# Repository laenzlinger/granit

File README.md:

# Granit — Offsite Backup Device

Custom carrier board for the Raspberry Pi CM4 Compute Module, designed as a minimal offsite backup appliance.

📖 **[Documentation](https://laenzlinger.github.io/granit/latest/)**

## Overview

A compact, headless device that connects to a remote network and receives encrypted backups
onto an attached hard disk. Designed to be left at a trusted offsite location and managed remotely.

- Raspberry Pi CM4 with PCIe SATA (ASM1061)
- 2.5" or 3.5" HDD/SSD support
- Software-controlled HDD power (GPIO)
- RTC wake for scheduled backups
- USB-C OTG for eMMC flashing
- Hammond 1455 aluminium enclosure

## Roadmap

- **v0.3** — First production run (CM4, 4-layer PCB, JLCPCB)
- **v0.4** — Fix wake/shutdown latch (#31), barrel jack swap (#40), DF40C alignment bosses (#37)
- **v1.0** — Validated design with custom OS image and documentation
- **Future** — Investigating RISC-V SoM support for a fully blob-free variant

## License

[CERN Open Hardware Licence Version 2 - Permissive](https://ohwr.org/cern_ohl_p_v2.txt)

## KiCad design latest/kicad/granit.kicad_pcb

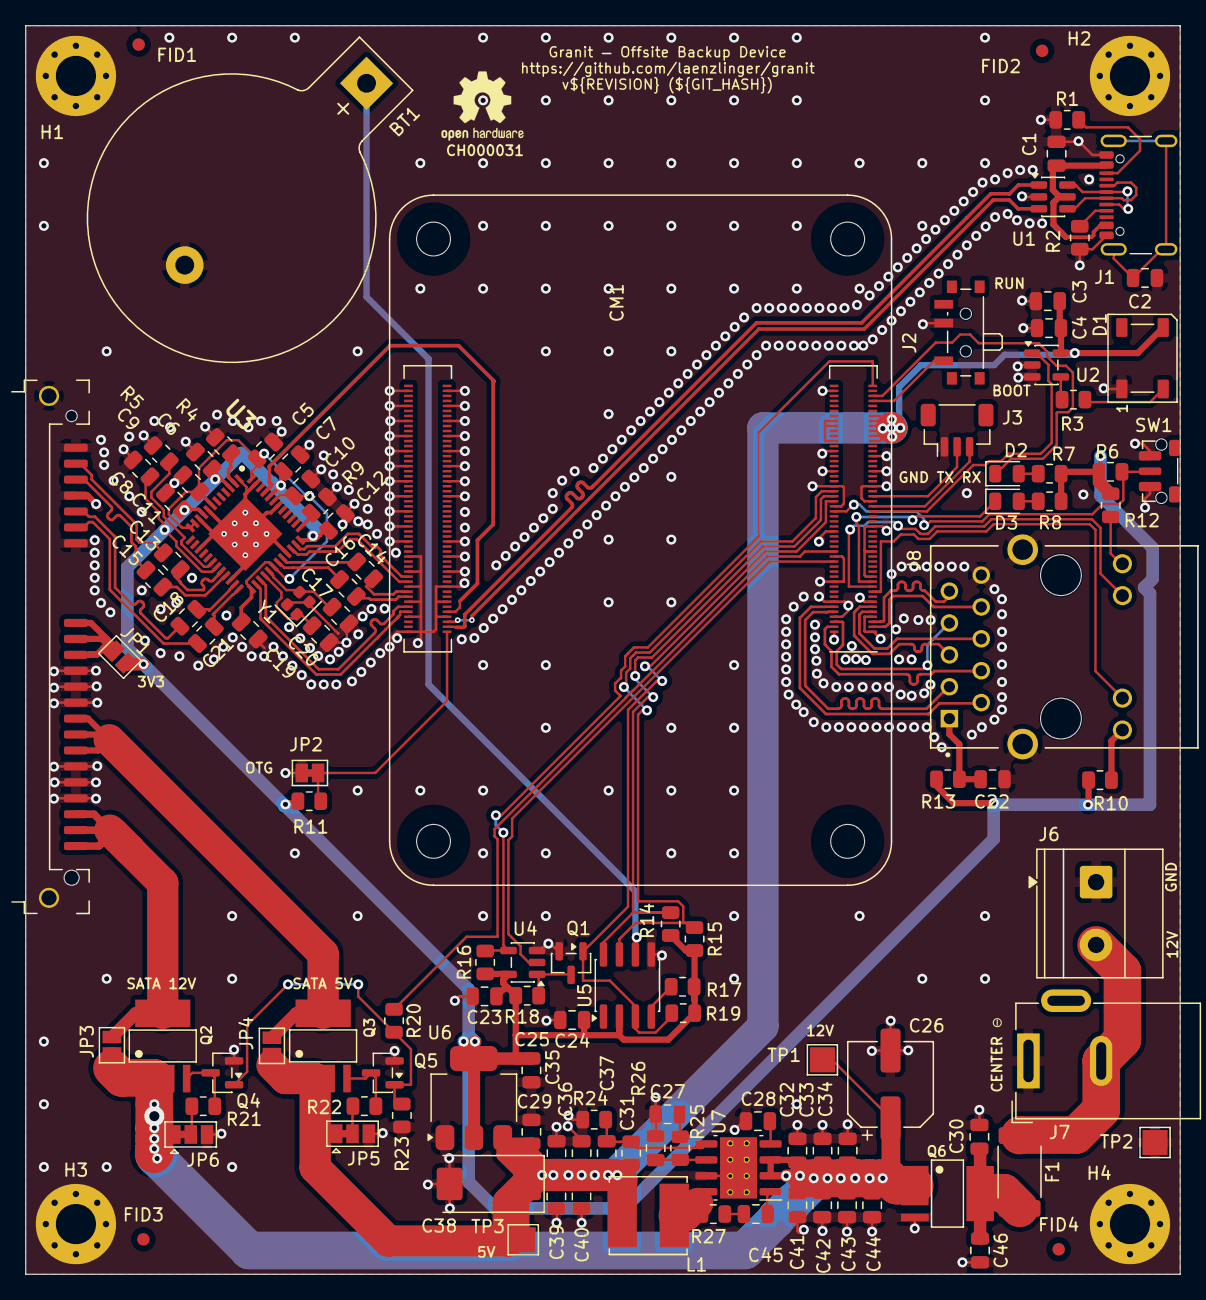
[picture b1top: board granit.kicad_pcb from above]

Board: 4 copper layers, 92.0 x 99.5 mm, 120 parts (0 on the bottom side), 87 nets.

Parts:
BT1: CR2032; BatteryHolder_Keystone_103_1x20mm
C1, C2, C3, C4, C5, C6, C7, C8, C9, C10, C11, C12, C13, C14, C15, C16, C18, C19, C21, C22, C23, C24, C28, C45: 100n; C_0805_2012Metric
C17, C20: 18p; C_0805_2012Metric
C25, C29, C30, C32, C33, C34, C35, C36, C39, C40, C41, C42, C43, C44, C46: 10u; C_0805_2012Metric
C26: 100uF/25V; CP_Elec_6.3x7.7
C27: 1.2n; C_0805_2012Metric
C31, C37: 1n; C_0805_2012Metric
C38: 100u; CP_EIA-7343-31_Kemet-D
CM1: CM4; Raspberry-Pi-4-Compute-Module
D1: WS2812B-5mm; LED_WS2812B_PLCC4_5.0x5.0mm_P3.2mm
D2: LED R; LED_0805_2012Metric
D3: LED G; LED_0805_2012Metric
F1: 3A; Fuse_2512_6332Metric
FID1, FID2, FID3, FID4: Fiducial; Fiducial_1mm_Mask2mm
H1, H2, H3, H4: MountingHole; MountingHole_3.2mm_M3_Pad_Via
J1: USB_C_Receptacle_USB2.0_14P; USB_C_Receptacle_GCT_USB4105-xx-A_16P_TopMnt_Horizontal
J2: PCM12SMTR; SW_SPDT_PCM12
J3: BM03B-SRSS-TB; JST_SH_BM03B-SRSS-TB_1x03-1MP_P1.00mm_Vertical
J4: SATA_22pin; SATA_Amphenol_10029364-001LF_Horizontal
J6: 12V Screw Terminal; TerminalBlock_Phoenix_MKDS-1,5-2_1x02_P5.00mm_Horizontal
J7: 12V Barrel; BarrelJack_Wuerth_6941xx301002
J8: HR911130A; HANRUN_HR911130A
JP1: 3V3_bridge; SolderJumper-2_P1.3mm_Open_Pad1.0x1.5mm
JP2: USB_OTG; SolderJumper-2_P1.3mm_Bridged_Pad1.0x1.5mm
JP3: 12V_bridge; SolderJumper-2_P1.3mm_Open_Pad1.0x1.5mm
JP4: 5V_bridge; SolderJumper-2_P1.3mm_Open_Pad1.0x1.5mm
JP5: SATA_5V_PWR; SolderJumper-3_P1.3mm_Bridged12_Pad1.0x1.5mm
JP6: SATA_12V_PWR; SolderJumper-3_P1.3mm_Bridged12_Pad1.0x1.5mm
L1: SRN6045TA-3R3Y; L_Bourns_SRN6045TA
Q1, Q4, Q5: 2N7002; SOT-23
Q2, Q3, Q6: FDS4435BZ; SO08-E3
R1, R2: 5K1; R_0805_2012Metric
R3, R7, R8, R10, R12: 330R; R_0805_2012Metric
R4, R26: 12K; R_0805_2012Metric
R5, R9: 750R; R_0805_2012Metric
R6, R11, R16, R17, R18, R19, R20: 10K; R_0805_2012Metric
R13, R27: 10R; R_0805_2012Metric
R14, R15: 4K7; R_0805_2012Metric
R21, R22, R23: 100K; R_0805_2012Metric
R24: 2K2; R_0805_2012Metric
R25: 20K; R_0805_2012Metric
SW1: SW_Push; SW_Push_1P1T-MP_NO_Horizontal_Alps_SKRTLAE010
SYM1: Logo_Open_Hardware_Large; OSHW-Logo2_7.3x6mm_SilkScreen
TP1, TP2, TP3: TestPoint; TestPoint_Pad_2.0x2.0mm
U1: USBLC6-2SC6; SOT-23-6
U2: 74AHCT1G125; SOT-23-5
U3: ASM1061; QFN50P700X700X90-49N-D
U4: 74AHCT1G32; SOT-23-5
U5: DS3231MZ; SOIC-8_3.9x4.9mm_P1.27mm
U6: NCP1117-3.3_SOT223; SOT-223-3_TabPin2
U7: AP64501SP-13; SOIC-8-1EP_3.9x4.9mm_P1.27mm_EP2.95x4.9mm_Mask2.71x3.4mm_Th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
Y1: 25MHz; Crystal_SMD_2016-4Pin_2.0x1.6mm

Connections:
+3V3: C6.1, C7.1, C8.1, C11.1, C12.1, C23.1, C24.1, C25.1, JP1.2 (B), R6.1, R7.2, R8.2, R10.1, R11.1, R12.1, R13.1, R14.2, R15.2, R16.1, R17.1, R18.1, R19.2, U3.3 (VCC33IN), U3.9 (VCC33_1), U3.19 (VCC33S), U3.36 (VCC33P), U3.44 (VCC33_2), U4.5 (VCC), U5.2 (VCC), U6.2 (VO)
+5VP: C3.1, C4.1, C29.1, C35.1, C36.1, C37.1, C38.1, C39.1, C40.1, CM1.77 (+5v_(Input)), CM1.79 (+5v_(Input)), CM1.81 (+5v_(Input)), CM1.83 (+5v_(Input)), CM1.85 (+5v_(Input)), CM1.87 (+5v_(Input)), D1.3 (VDD), JP4.2 (B), JP5.1 (A), L1.2, Q3.1-3, R26.1, TP3.1 (1_1), U2.5 (VCC), U6.3 (VI)
+12VP: C26.1, C32.1, C33.1, C34.1, C41.1, C42.1, C43.1, C44.1, JP3.2 (B), JP6.1 (A), Q2.1-3, Q6.1-3, TP1.1 (1_1), U7.2 (VIN), U7.3 (EN)
/Power Supply/fused: C30.1, C46.1, F1.2, Q6.5-8
/Power Supply/switch: L1.1, R27.1, U7.8 (SW)
/Power Supply/unfused: F1.1, J6.2, J7.2
/SATA Bridge/+5V_S: J4.P7 (+5V), J4.P8 (+5V), J4.P9 (+5V), JP4.1 (A), Q3.5-8
/SATA Bridge/+12V_S: J4.P13 (+12V), J4.P14 (+12V), J4.P15 (+12V), JP3.1 (A), Q2.5-8
/SATA Bridge/PCIE_D_RX_N: C14.1, U3.32 (PRXN)
/SATA Bridge/PCIE_D_RX_P: C16.1, U3.31 (PRXP)
/SATA Bridge/SATA_A_RX_N: C18.2, J4.S5 (RX-)
/SATA Bridge/SATA_A_RX_P: C21.2, J4.S6 (RX+)
/SATA Bridge/SATA_A_TX_N: C15.2, J4.S3 (TX-)
/SATA Bridge/SATA_A_TX_P: C13.2, J4.S2 (TX+)
/SATA Bridge/SATA_D_RX_N: C18.1, U3.23 (SRXN_A)
/SATA Bridge/SATA_D_RX_P: C21.1, U3.24 (SRXP_A)
/SATA Bridge/SATA_D_TX_N: C15.1, U3.21 (STXN_A)
/SATA Bridge/SATA_D_TX_P: C13.1, U3.20 (STXP_A)
BUTTON: CM1.50 (GPIO17), R6.2, SW1.2
ETH_P0_N: CM1.10 (Ethernet_Pair0_N), J8.3 (TD1-)
ETH_P0_P: CM1.12 (Ethernet_Pair0_P), J8.2 (TD1+)
ETH_P1_N: CM1.6 (Ethernet_Pair1_N), J8.7 (TD2-)
ETH_P1_P: CM1.4 (Ethernet_Pair1_P), J8.4 (TD2+)
ETH_P2_N: CM1.9 (Ethernet_Pair2_N), J8.6 (TD3-)
ETH_P2_P: CM1.11 (Ethernet_Pair2_P), J8.5 (TD3+)
ETH_P3_N: CM1.5 (Ethernet_Pair3_N), J8.9 (TD4-)
ETH_P3_P: CM1.3 (Ethernet_Pair3_P), J8.8 (TD4+)
ETH_nLED1: CM1.19 (Ethernet_nLED1(3.3v)), J8.13
ETH_nLED2: CM1.17 (Ethernet_nLED2(3.3v)), J8.12
GLOBAL_EN: CM1.99 (Global_EN), R16.2, U4.4
GND: BT1.2 (-), C1.2, C2.2, C3.2, C4.2, C5.2, C6.2, C7.2, C8.2, C9.2, C10.2, C11.2, C12.2, C17.2, C19.2, C20.2, C22.2, C23.2, C24.2, C25.2, C26.2, C27.2, C28.2, C29.2, C30.2, C31.2, C32.2, C33.2, C34.2, C35.2, C36.2, C38.2, C39.2, C40.2, C41.2, C42.2, C43.2, C44.2, C46.2, CM1.1 (GND), CM1.2 (GND), CM1.7 (GND), CM1.8 (GND), CM1.13 (GND), CM1.14 (GND), CM1.22 (GND), CM1.23 (GND), CM1.32 (GND), CM1.33 (GND), CM1.42 (GND), CM1.43 (GND), CM1.52 (GND), CM1.53 (GND), CM1.59 (GND), CM1.60 (GND), CM1.65 (GND), CM1.66 (GND), CM1.71 (GND), CM1.74 (GND), CM1.98 (GND), CM1.102 (PCIe_CLK_nREQ), CM1.107 (GND), CM1.108 (GND), CM1.113 (GND), CM1.114 (GND), CM1.119 (GND), CM1.120 (GND), CM1.125 (GND), CM1.126 (GND), CM1.131 (GND), CM1.132 (GND), CM1.137 (GND), CM1.138 (GND), CM1.144 (GND), CM1.150 (GND), CM1.155 (GND), CM1.156 (GND), CM1.161 (GND), CM1.162 (GND), CM1.167 (GND), CM1.168 (GND), CM1.173 (GND), CM1.174 (GND), CM1.179 (GND), CM1.180 (GND), CM1.185 (GND), CM1.186 (GND), CM1.191 (GND), CM1.192 (GND), CM1.197 (GND), CM1.198 (GND), D1.1 (VSS), H1.1 (1_1), H2.1 (1_1), H3.1 (1_1), H4.1 (1_1), J1.A1 (GND), J1.A12 (GND), J1.B1 (GND), J1.B12 (GND), J2.2 (C), J3.1, J4.MP (SHIELD), J4.P4 (GND), J4.P5 (GND), J4.P6 (GND), J4.P10 (GND), J4.P11 (GND), J4.P12 (GND), J4.S1 (S1_GND), J4.S4 (S4_GND), J4.S7 (S7_GND), J6.1, J7.1, J8.10 (GND), J8.S1 (SH), J8.S2 (SH), JP2.1 (A), JP5.3 (B), JP6.3 (B), Q1.2 (S), Q4.2 (S), Q5.2 (S), Q6.4, R1.1, R2.2, R4.1, R5.1, R9.2, R23.1, R24.2, SW1.1, TP2.1 (1_1), U1.2 (GND), U2.2, U2.3 (GND), U3.1 (VSSPWM), U3.8 (GND_1), U3.10 (GND_2), U3.15 (GNDA_1), U3.22 (GNDA_2), U3.33 (GNDA_3), U3.42 (GND_3), U3.47 (TESTMODE), U3.49 (EP), U4.3 (GND), U5.5 (GND), U6.1 (GND), U7.7 (GND), U7.9 (EP), Y1.2 (G), Y1.4 (G)
GPIO_HOLD: CM1.30 (GPIO6), U4.2
NEOPIXEL: CM1.49 (GPIO18), U2.1
unnamed: BT1.1 (+), U5.6 (VBAT)
unnamed: C27.1, R25.2
unnamed: C45.1, R27.2
unnamed: CM1.78 (GPIO_VREF(1.8v/3.3v_Input)), CM1.84 (+3.3v_(Output)), CM1.86 (+3.3v_(Output))
unnamed: D1.2 (DIN), R3.2
unnamed: D2.2 (A), R7.1
unnamed: D3.2 (A), R8.1
unnamed: J1.A5 (CC1), R2.1
unnamed: J1.B5 (CC2), R1.2
unnamed: J1.A6 (D+), J1.B6 (D+), U1.4 (I/O2)
unnamed: J1.A7 (D-), J1.B7 (D-), U1.6 (I/O1)
unnamed: C2.1, J1.SH (SHIELD)
unnamed: C22.1, J8.1 (CT_PRI), R13.2
unnamed: J8.11, R10.2
unnamed: J8.14, R12.2
unnamed: J4.P1 (+3.3V), J4.P2 (+3.3V), J4.P3 (+3.3V), JP1.1 (A)
unnamed: JP5.2 (C), R22.1
unnamed: JP6.2 (C), R21.1
unnamed: Q1.3 (D), R18.2, U4.1
unnamed: Q2.4, Q4.3 (D), R21.2
unnamed: Q4.1 (G), Q5.1 (G), R20.1, R23.2
unnamed: Q3.4, Q5.3 (D), R22.2
unnamed: R3.1, U2.4
unnamed: C1.1, J1.A4 (VBUS), J1.A9 (VBUS), J1.B4 (VBUS), J1.B9 (VBUS), U1.5 (VBUS)
unnamed: R4.2, U3.2 (EXTL)
unnamed: R9.1, U3.37 (PREXT)
unnamed: R5.2, U3.18 (SREXT)
unnamed: C5.1, C9.1, C10.1, C19.1, U3.7 (VCC12_1), U3.11 (VCC12_2), U3.12 (VDD12S_1), U3.25 (VDD12S_2), U3.30 (VDD12P), U3.43 (VCC12_3), U3.48 (VCC12_4)
unnamed: C17.1, U3.29 (XI), Y1.3
unnamed: C20.1, U3.28 (XO), Y1.1
unnamed: R17.2, U5.4 (~RST)
unnamed: C45.2, U7.1 (BST)
unnamed: C31.1, R25.1, U7.6 (COMP)
unnamed: C37.2, R24.1, R26.2, U7.5 (FB)
unnamed: C28.1, U7.4 (SS)
PCIE_CLK_N: CM1.112 (PCIe_CLK_N), U3.27 (PECLKN)
PCIE_CLK_P: CM1.110 (PCIe_CLK_P), U3.26 (PECLKP)
PCIE_RX_N: C14.2, CM1.118 (PCIe_RX_N)
PCIE_RX_P: C16.2, CM1.116 (PCIe_RX_P)
PCIE_TX_N: CM1.124 (PCIe_TX_N), U3.35 (PTXN)
PCIE_TX_P: CM1.122 (PCIe_TX_P), U3.34 (PTXP)
PCIE_nRST: CM1.109 (PCIe_nRST), U3.45 (PERST#)
RTC_INT: CM1.54 (GPIO4), Q1.1 (G), R19.1, U5.3 (~INT/SQW)
SATA_PWR_EN: CM1.34 (GPIO5), R20.2
SCL1: CM1.56 (GPIO3), R14.1, U5.8 (SCL)
SDA1: CM1.58 (GPIO2), R15.1, U5.7 (SDA)
UART_RX: CM1.51 (GPIO15), J3.3
UART_TX: CM1.55 (GPIO14), J3.2
USB_DN: CM1.103 (USB2_N), U1.1 (I/O1)
USB_DP: CM1.105 (USB2_P), U1.3 (I/O2)
USB_OTG_ID: CM1.101 (USB_OTG_ID), JP2.2 (B), R11.2
nLED_ACT: CM1.21 (PI_nLED_Activity), D3.1 (K)
nLED_PWR: CM1.95 (nPI_LED_PWR), D2.1 (K)
nRPIBOOT: CM1.93 (nRPIBOOT), J2.1 (B)

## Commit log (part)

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2026-04-17 Deploying to gh-pages from @ laenzlinger/granit@0618c86b285749e74d22a0283d2c9999025c9fad 🚀
2026-04-17 Deploying to gh-pages from @ laenzlinger/granit@da1aa1df934bb73ba960f90b383189d1a577e9dc 🚀
2026-04-17 Deploying to gh-pages from @ laenzlinger/granit@532a676b9b509b506f28b5e1680c126269413395 🚀
2026-04-17 Fix end plate transform offsets for both case variants
2026-04-17 Deploying to gh-pages from @ laenzlinger/granit@4f9f17914b38426bdd78a7d190837a975e7716cf 🚀
2026-04-18 Update assembly screenshots (f3d render with end plate cutouts)
2026-04-18 Deploying to gh-pages from @ laenzlinger/granit@67baf37ae4077ac6b6636a26d672a4660777e54b 🚀
2026-04-18 Add identity transform to EndPlate item (o3dv requires it)
2026-04-18 Deploying to gh-pages from @ laenzlinger/granit@d2b397f8ced72ffb720f871b6108930d67110e21 🚀
2026-04-18 Remove 3MF files (STL for printing, DXF for CNC, STEP for viewer)
2026-04-18 STEP-only assembly: remove Z-up flip and 3MF export
2026-04-18 Deploying to gh-pages from @ laenzlinger/granit@9f0a0611937969795056b851993d5350d8d3886f 🚀
2026-04-18 Deploying to gh-pages from @ laenzlinger/granit@68356a7168c3dc9b7aa0843cc9bb36ea58668e00 🚀
2026-04-18 Match f3d screenshot camera angle to o3dv default view
2026-04-18 Deploying to gh-pages from @ laenzlinger/granit@ae3af33d56b08c6f37729c447657eb5fa37ac692 🚀
2026-04-18 Deploying to gh-pages from @ laenzlinger/granit@67168523b74eab0df490270680dec928d598fd00 🚀
2026-04-18 Update Makefiles and add mise/node for screenshot toolchain
    - mise: add node for puppeteer dependency
    - mechanical/Makefile: add end-plates target (STL+DXF), fix comments
    - mechanical/package.json: puppeteer dependency
    - screenshot via o3dv headless Chromium
2026-04-18 Deploying to gh-pages from @ laenzlinger/granit@98eaa93e1e670243ace4d96b4a713b2be834b8f0 🚀
2026-04-18 Deploying to gh-pages from @ laenzlinger/granit@0353b88d7bfc0207eb91483b42f5445857eb0097 🚀
2026-04-18 Remove all rotation — native Y-up, o3dv handles it correctly
2026-04-18 Deploying to gh-pages from @ laenzlinger/granit@45cf383ca316f8a3436c6b29f0f1e6ae217baa8c 🚀
2026-04-18 Fix Makefile component filter to match PCB export
2026-04-18 kibot: diff against v0.3.0 (KIBOT_TAG-1 broken on non-tag builds)
2026-04-18 Deploying to gh-pages from @ laenzlinger/granit@1b6a4ec26f31289ce8aaa81f857986ff5dfea080 🚀
2026-04-18 Deploying to gh-pages from @ laenzlinger/granit@b21923f2273eddeb64ed79310c8566ec3a780e53 🚀
2026-04-18 Add assembly screenshots inline after enclosure variants
2026-04-18 Deploying to gh-pages from @ laenzlinger/granit@d8e7f161ab54b39170917479dff0fcb476b8d4e9 🚀
2026-04-18 Add RPi undervoltage/throttle metrics from nas-infra
    Exports vcgencmd throttle flags as Prometheus metrics via
    node-exporter textfile collector. Runs every 30s. Detects
    under-voltage conditions critical for remote monitoring.
2026-04-18 Refactor: split pi-gen (image) and Ansible (configuration)
    pi-gen: minimal image with packages + boot config only
    Ansible: all services, security, monitoring, sync script
    Benefits:
    - Can provision stock Raspberry Pi OS without custom image
    - Configuration changes don't require image rebuild
    - Same tooling as nas-infra project
2026-04-18 Deploying to gh-pages from @ laenzlinger/granit@e8a9da2c5a01cdf1be6ab6a2698d6edd3a4b684a 🚀
2026-04-18 Deploying to gh-pages from @ laenzlinger/granit@9be59a5ab2dda39324600b26048d8e69cf1b3577 🚀
2026-04-18 Deploying to gh-pages from @ laenzlinger/granit@528a2d54a39709b47c2c5dfb1e440e62ac837035 🚀
2026-04-18 Deploying to gh-pages from @ laenzlinger/granit@7ec95b2356015831294d18c5967b5c21f3bebc21 🚀
2026-04-21 ci: trigger rebuild for diff generation
2026-04-21 site: update theme to show diffs on latest builds
2026-04-21 remove local render target, replaced by KiBot blender_export
2026-04-21 Deploying to gh-pages from @ laenzlinger/granit@866a566c5ca0ea9deb9ec5448e72c4771d55a9fb 🚀
2026-04-21 ci: trigger rebuild after workflow fix
2026-04-21 remove outdated static 3D render
2026-04-21 Deploying to gh-pages from @ laenzlinger/granit@16880526b0f03d426e12aaad02cfae33f1aad8fe 🚀
2026-04-21 Deploying to gh-pages from @ laenzlinger/granit@b561ba60108319ee5f10cec701559c64e448490b 🚀
2026-04-21 site: pin hugo-kicad-site v1.0.1
2026-04-21 blender: match Z rotation for top and bottom views
2026-04-21 site: update hugo-kicad-site to v1.0.2
2026-04-21 ci: remove kibot_install (3D models now cached by workflow)
2026-04-21 site: add use case description with 3-2-1 backup rule
2026-04-21 site: move architecture diagram to site static
2026-04-22 ci: re-add kicad-packages3d install (GitLab 3D downloads fail for KiCad 10)
2026-04-22 Deploying to gh-pages from @ laenzlinger/granit@4e5d9a8812deee8d22ae43165caa37b790262820 🚀
2026-04-22 Remove kibot_install and container_image (now defaults in reusable workflow)
2026-04-22 Reduce Blender render resolution to QHD (2560x1440)
2026-04-22 Update theme (transparent assembly viewer background)
2026-04-22 Add cairn logo as favicon
2026-04-23 Deploying to gh-pages from @ laenzlinger/granit@6adc57956b9adb32f3bc73c34f09a668fba13e19 🚀
2026-04-23 Simplify architecture diagram
2026-04-23 Deploying to gh-pages from @ laenzlinger/granit@28a4abfb4317807c7911916e079056aa2ab9460f 🚀
2026-04-23 Deploying to gh-pages from @ laenzlinger/granit@9c7c9311b7486694a20e02296c61d6fa456c25ba 🚀
2026-04-24 fix: correct SATA slot position on HDD models and align drive to connector
    The SATA connector on HDDs is offset ~16-19mm from the drive center
    (per SFF-8201/8301). The previous HDD models had incorrectly sized and
    positioned slots, and the assembly centered the drive body instead of
    aligning the SATA connector with J4 on the PCB.
    Changes:
    - Add mechanical/hdd.scad (OpenSCAD parametric HDD model)
2026-04-24 Deploying to gh-pages from @ laenzlinger/granit@f994fe32861f9e128897c0b4695d907eee013e28 🚀
2026-04-25 site: add v0.3.0 slim case fit warning (issue #1)
2026-04-25 pnp: add feeder map generation instructions
2026-04-25 Deploying to gh-pages from @ laenzlinger/granit@7d908ce97757cd4597e9a7e658aeb698e23b4ed5 🚀
2026-04-25 site: add stencil jig STL download link
2026-04-25 Deploying to gh-pages from @ laenzlinger/granit@36e59cbd7e8a4c18991d4ab947e7a4610ac94a5f 🚀
2026-04-25 Deploying to gh-pages from @ laenzlinger/granit@ffcc43642c6177beedc31a0fc089dcef7215bc7b 🚀
2026-04-25 Deploying to gh-pages from @ laenzlinger/granit@e8ca3d28c1f9397ebdefc6d01ec5a6bd42bafc52 🚀
2026-04-25 Deploying to gh-pages from @ laenzlinger/granit@995e122e4e72fd859809d003af27c35a95b41976 🚀
2026-04-25 Deploying to gh-pages from @ laenzlinger/granit@ab0b8bbaf4be3e805a5e4588a9bafdbdd201013d 🚀
2026-04-25 Deploying to gh-pages from @ laenzlinger/granit@aa11529f792f9ef08f11d93b15656f45e04e4c6f 🚀
2026-04-25 Deploying to gh-pages from @ laenzlinger/granit@cbcf62ac12211bdb459baec58c0feeebae8135d7 🚀
2026-04-26 Deploying to gh-pages from @ laenzlinger/granit@cfbe25b3f49500ae832e82f3d09b496575dc9c08 🚀
2026-04-26 pnp: remove drag feeders, use strip feeders only
2026-04-26 Deploying to gh-pages from @ laenzlinger/granit@e8e177deece2461416e31604cf12785c9b6ccd4d 🚀
2026-04-26 pnp: use openpnp-tools generate instead of Python remap script
2026-04-26 pnp: add ensure-parts to make pnp pipeline
2026-04-26 Deploying to gh-pages from @ laenzlinger/granit@e2dd62a7d18ee58b36b5bc093072ed09eb740e9a 🚀
2026-04-26 Deploying to gh-pages from @ laenzlinger/granit@b98ed56b67a830639b6abe7bb9fbad74838db38f 🚀
2026-04-27 pnp: add PCM12SMTR, SKRTLAE010, 100uF to machine placement
2026-04-27 Deploying to gh-pages from @ laenzlinger/granit@285d4b6b2c9d1d32a6c2daa9ca88f9184ef15b0a 🚀
2026-04-28 Deploying to gh-pages from @ laenzlinger/granit@d26a16ac7dd40f54040b7d6900b76d8f110cad32 🚀
2026-05-01 chore: sort feeders by ascending component value
2026-05-01 Deploying to gh-pages from @ laenzlinger/granit@4261cd83f4c561cfef4520b3d7d811a16a6fb59d 🚀
2026-05-01 update feeder map with corrected IC tape types
2026-05-01 update feeder map: fix WS2812B tape type to BlackPlastic
2026-05-01 update feeder map: fix SOT-23-5 tape type to BlackPlastic
2026-05-01 Deploying to gh-pages from @ laenzlinger/granit@e489a2ce589f230cca5a2f0201bb4fe250f40f38 🚀
2026-05-01 renumber 16mm feeders to close gap after TANT-D move
2026-05-01 Deploying to gh-pages from @ laenzlinger/granit@b58dce1c36dbb95f66a028b0986418eaf03e3d60 🚀
2026-05-01 Deploying to gh-pages from @ laenzlinger/granit@6781db9b740504d36322780dd12701e2e18d164b 🚀
2026-05-01 pnp: set board Z=8.7mm, enable fiducial check
2026-05-01 pnp: correct board Z to 8.6mm
2026-05-01 Deploying to gh-pages from @ laenzlinger/granit@798a164d5036b8835d346bdc57794bb96ecfde14 🚀
2026-05-02 fix: correct R17/R19 silkscreen label positions
    Fixes #34
2026-05-03 Deploying to gh-pages from @ laenzlinger/granit@08f6d466d5cfc5943391063ddbe4d5b5bb4c0d6f 🚀
2026-05-03 Deploying to gh-pages from @ laenzlinger/granit@60b38995608a7f280077a7f7a40105f83e0307bd 🚀
2026-05-03 fix: update assembly comment — SATA connector is centered on HDD
2026-05-03 Deploying to gh-pages from @ laenzlinger/granit@2d33c95f3b09e26c2d32af32065ab2bf9836499e 🚀
2026-05-03 Deploying to gh-pages from @ laenzlinger/granit@6952ebacc9b41ed3805883d4e85b93718a621cb5 🚀
2026-05-06 Deploying to gh-pages from @ laenzlinger/granit@89f85b2f28da9fc67ecb7cc1cdc079b62310a36e 🚀
2026-05-06 Pin theme to v1.1.0 (Hextra)
2026-05-06 Deploying to gh-pages from @ laenzlinger/granit@5f8a60bc6ede95407f85217dd60725f6aa42da34 🚀
2026-05-06 Deploying to gh-pages from @ laenzlinger/granit@6bfa76459a644eccfd845e2622477bc1d1cca0e8 🚀
2026-05-06 wip: compact sandwich assembly PoC (issue #30)
    Simplified parametric 1455N1601 case model (OpenSCAD).
    Sandwich stack-up: HDD on bottom, PCB above, 10.3mm margin.
    PCB/HDD orientation still needs fixing.
2026-05-07 docs: diagonal pin placement for DF40C jig (#39)
2026-05-07 Deploying to gh-pages from @ laenzlinger/granit@a1fa605b2bb5a82fd845bf595ec759a231ee2605 🚀
2026-05-10 Deploying to gh-pages from @ laenzlinger/granit@4fc6703c044900f5c58001c9b430c613706c5e99 🚀
2026-05-10 Deploying to gh-pages from @ laenzlinger/granit@246e3970a8d90b31ddf7f1ea44d4cac3fcf5511b 🚀
2026-05-10 Deploying to gh-pages from @ laenzlinger/granit@95885a71099e6f62d2ce23189c9e53067ebba65e 🚀
2026-05-10 Deploying to gh-pages from @ laenzlinger/granit@0817726e587c68c2899bff6f0e5998b53e06b621 🚀
2026-05-13 Update reflow method: hot plate → reflow oven
2026-05-14 Add logo to navbar (reuse favicon SVG)
2026-05-16 mechanical: switch compact sandwich to 1455T1601 (165mm wide)
    The 1455N (103mm) internal width is too narrow for a 3.5" HDD (101.6mm).
    Switch to 1455T1601 (165×51.5×160mm) which has 162mm internal width.
    Stack-up: 39.7mm total, 48.5mm available, 8.8mm margin.
    HDD fits with 60mm spare width and 13mm spare length.
2026-05-16 mechanical: move generated files to out/ subdirectory
    All generated STL, STEP, and GLB files now go to mechanical/out/
    which is gitignored. Source files (OpenSCAD, Python) stay in mechanical/.
2026-05-16 mechanical: unified assembly style for all variants
    All three assemblies now show:
    - Case body offset to the side
    - Belly plate in position
    - End plates at both ends
    - PCB + HDD in correct positions
    All case parts generated from our parametric 1455-case.scad.
2026-05-16 mechanical: tune assembly positions and boss diagonal width
    - Align PCB and HDD with end plate cutouts in all variants
    - Diagonal boss cutout width matches belly plate slot (1.7mm)
    - Compact end plate with cutouts for sandwich layout
2026-05-16 mechanical: remove old tracked generated files
    These are now generated into out/ which is gitignored.
2026-05-16 Deploying to gh-pages from @ laenzlinger/granit@4f172abe6c3b1b159b6c8cf89108c772fb962f43 🚀
2026-05-16 site: move enclosure variants table to top of assembly page
